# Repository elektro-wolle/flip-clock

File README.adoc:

= Copal Flip-Clock 

Antriebsrad (1 Umdrehung = 1 Stunde): ca. 82 Zähne  +
Stepper 12 Zähne  +
1 Minute = 6° * 82/11 = 41° Stepper 

Schritt-Schema: 3 Vollschritte zurück (Rutschkupplung nutzen) -> 1 Schritt vorwärts.

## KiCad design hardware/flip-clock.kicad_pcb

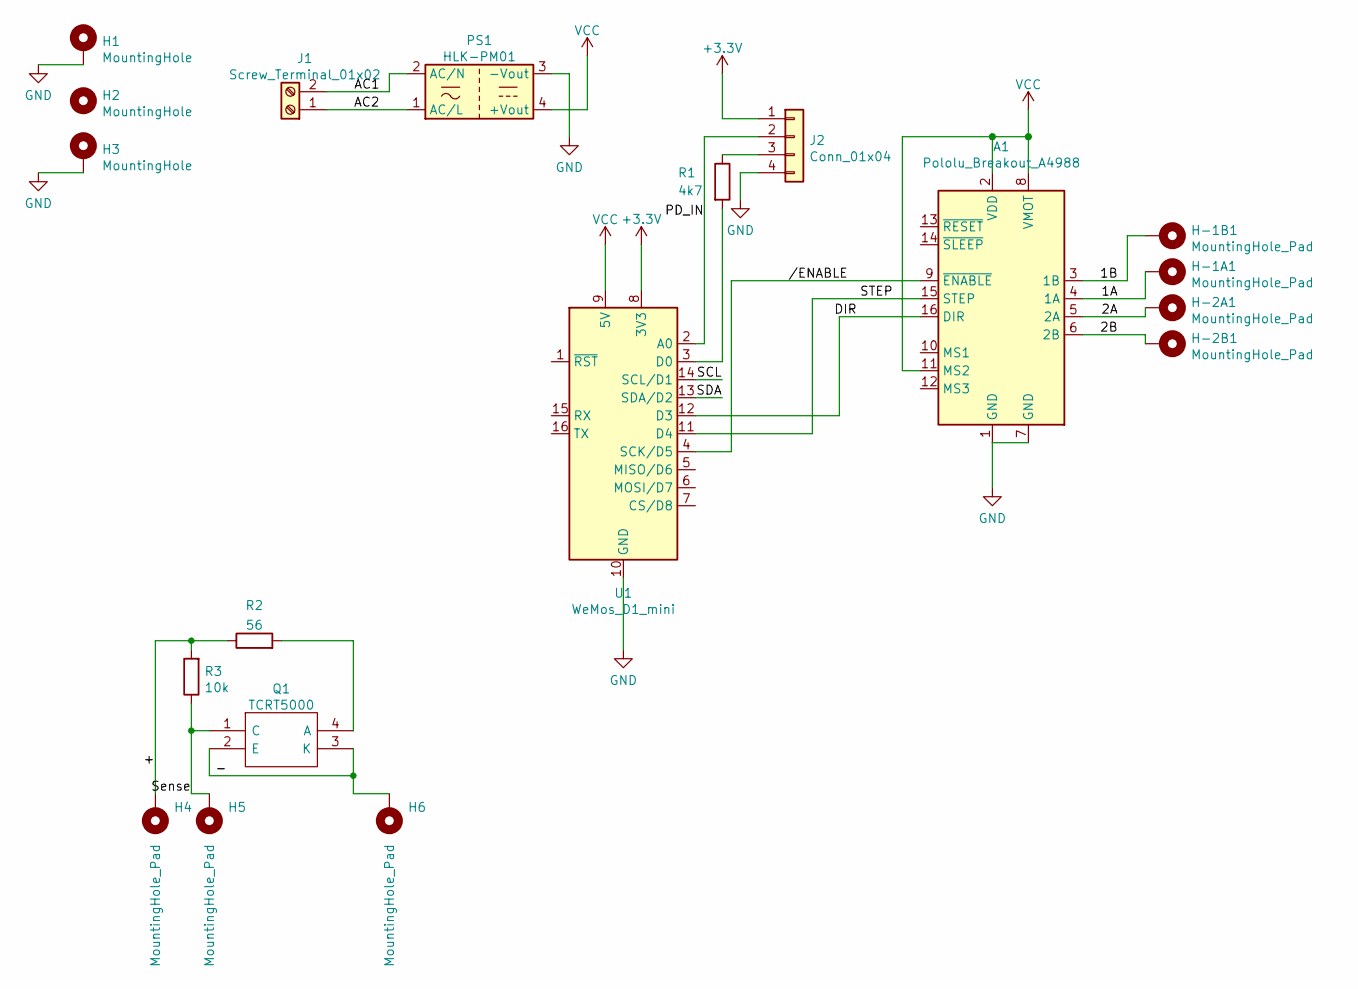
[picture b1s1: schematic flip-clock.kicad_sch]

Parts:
A1: Pololu_Breakout_A4988; Pololu_Breakout-16_15.2x20.3mm
H1, H3: MountingHole; MountingHole_3.2mm_M3_Pad
H2: MountingHole; MountingHole_5.3mm_M5
H4, H5, H6: MountingHole_Pad; SolderWirePad_1x01_SMD_1x2mm
H-1A1, H-1B1, H-2A1, H-2B1: MountingHole_Pad; SolderWire-0.1sqmm_1x01_D0.4mm_OD1mm
J1: Screw_Terminal_01x02; TerminalBlock_Phoenix_MKDS-1,5-2_1x02_P5.00mm_Horizontal
J2: Conn_01x04; JST_PH_B4B-PH-K_1x04_P2.00mm_Vertical
PS1: HLK-PM01; Converter_ACDC_HiLink_HLK-PMxx
Q1: TCRT5000; Manufacturer_Part_Number TCRT5000; Mouser Part Number 782-TCRT5000
R1: 4k7; R_0805_2012Metric
R2: 56; R_0805_2012Metric
R3: 10k; R_0805_2012Metric
U1: WeMos_D1_mini; WEMOS_D1_mini_light

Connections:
+3V3: J2.1, U1.8 (3V3)
/1A: A1.4 (1A), H-1A1.1
/1B: A1.3 (1B), H-1B1.1
/2A: A1.5 (2A), H-2A1.1
/2B: A1.6 (2B), H-2B1.1
/+: H4.1, R2.1, R3.2
/-: H6.1, Q1.2 (E), Q1.3 (K)
/AC1: J1.2, PS1.2 (AC/N)
/AC2: J1.1, PS1.1 (AC/L)
/DIR: A1.16 (DIR), U1.12 (D3)
/PD_IN: J2.2, U1.2 (A0)
/SCL: U1.14 (SCL/D1)
/SDA: U1.13 (SDA/D2)
/STEP: A1.15 (STEP), U1.11 (D4)
/Sense: H5.1, Q1.1 (C), R3.1
//ENABLE: A1.9 (~ENABLE), U1.4 (SCK/D5)
GND: A1.1 (GND), A1.7 (GND), H1.1, H3.1, J2.4, PS1.3 (-Vout), U1.10 (GND)
unnamed: J2.3, R1.1
unnamed: Q1.4 (A), R2.2
unnamed: R1.2, U1.3 (D0)
VCC: A1.2 (VDD), A1.8 (VMOT), A1.11 (MS2), PS1.4 (+Vout), U1.9 (5V)

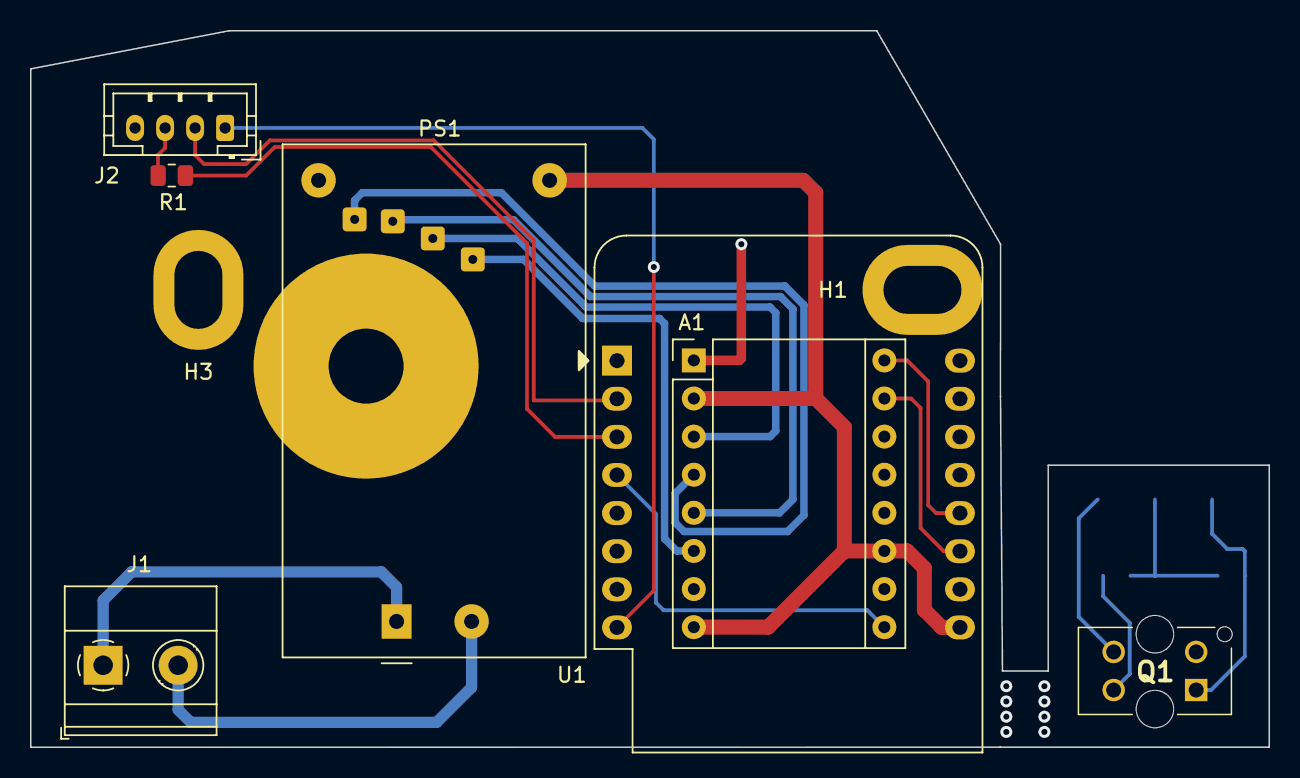
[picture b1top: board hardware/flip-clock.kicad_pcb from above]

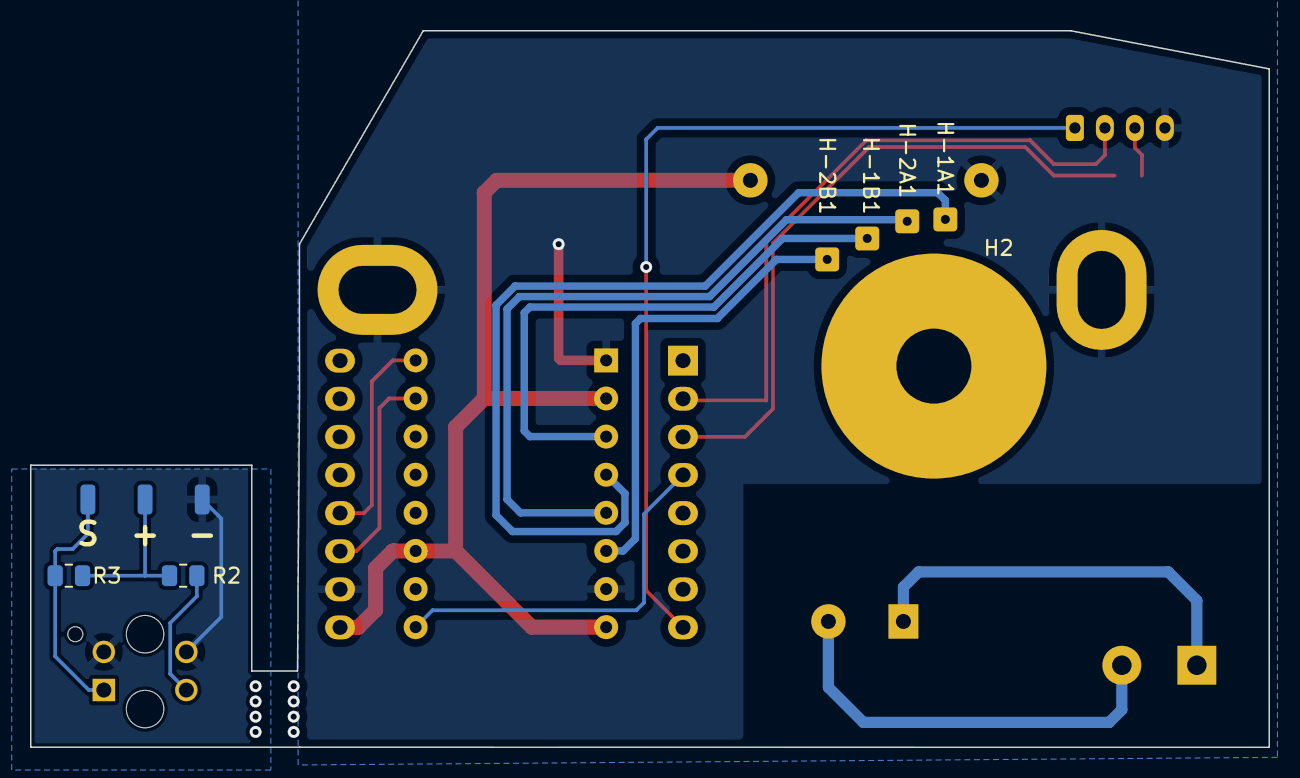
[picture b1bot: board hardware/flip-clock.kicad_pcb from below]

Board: 2 copper layers, 82.6 x 47.8 mm, 19 parts (6 on the bottom side), 19 nets.

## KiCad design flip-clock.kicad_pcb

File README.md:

Bei dieser schönen 60er-Jahre Uhr war der Synchronmotor defekt (lief nur
selten an, Versatz von 2h pro Tag). Ein Ersatz für diesen war nicht zu
finden, daher die High-Tech-Variante.

-   Synchronmotor durch Schrittmotor ersetzen

-   Zeit via NTP über einen ESP holen

-   Das Ganze so, dass es ein 1:1 Ersatz zu dem montierten Motor wird

# Herausforderungen

-   Einen Schrittmotor finden mit passendem Ritzel und passender Größe.

-   Der Schrittmotor mit passendem Ritzel ist für max. 5V ausgelegt, die
    üblichen StepSticks brauchen 8V.

-   Alles in das Gehäuse bekommen.

-   Erste Tests zeigten, dass für eine Minute eine unterschiedliche
    Anzahl an Schritten benötigt wird.

-   Keine Möglichkeit, das Umspringen der Minuten zu erkennen.

-   Spontane Abschaltungen bei Netzbetrieb.

# Lösungen

## Schrittmotor

AliExpress sei Dank: [Stepper-Motor mit 12 Zähnen und Modul
0,25](https://www.aliexpress.com/item/4001009328124.html).

## StepStick

Natürlich gibt es was von [Trinamic](https://www.trinamic.com) auf Basis
des [TMC2225
Datasheet](https://www.trinamic.com/fileadmin/assets/Products/ICs_Documents/TMC2225_Datasheet_Rev1.11.pdf).
Zum Beispiel [hier](https://www.amazon.de/dp/B08R3GFYTR).

## Platine produzieren

Millimetergenaues Ausmessen, KiCad, Aisler:

## Schritte zählen

Aufgrund des doch sehr beschränkten Platzes, blieb nur die Möglichkeit
übrig, die bestehende Glimmmlampe auszubauen und stattdessen eine kleine
Reflex-Lichtschranke (TCRT-5000) anzubringen. Diese löst recht
zuverlässig auf, wenn sich ein Blatt der Minuten-Anzeige im Fallen
befindet.

## Spontane Resets

Ein 100uF Kondensator auf der 5V Schiene wirkt Wunder:

## Fertiger Aufbau

## Zusammenbau

# Software

Kleines C++ Projekt mit platformio auf Basis der Bibliotheken:
[WiFiManager](https://github.com/tzapu/WiFiManager),
[AceTime](https://github.com/bxparks/AceTime),
[ESP_DoubleResetDetector](https://github.com/khoih-prog/ESP_DoubleResetDetector).

Lösung ist straight-forward: Intern wird die vermutlich angezeigte Zeit
(durch das Zählen via IR-Reflex-Lichtschranke) mit der via NTP
empfangenen Zeit verglichen und solange der Stepper-Motor aktiviert, bis
diese übereinstimmen.

Dabei eine Sonderbehandlung für kleine Abweichungen (bis 10 Minuten wird
einfach gewartet, bis die Zeit übereinstimmt) und in der Nacht (z.B. Bei
der Sommer-/Winterzeit-Umstellung müssten 23 Stunden nach vorne gestellt
werden).

Über eine minimale Web-Oberfläche kann bei Stromausfall oder ähnlichem
die tatsächlich angezeigte Uhrzeit angegeben werden. Code siehe
[Quellcode](sw/src/main.cpp).

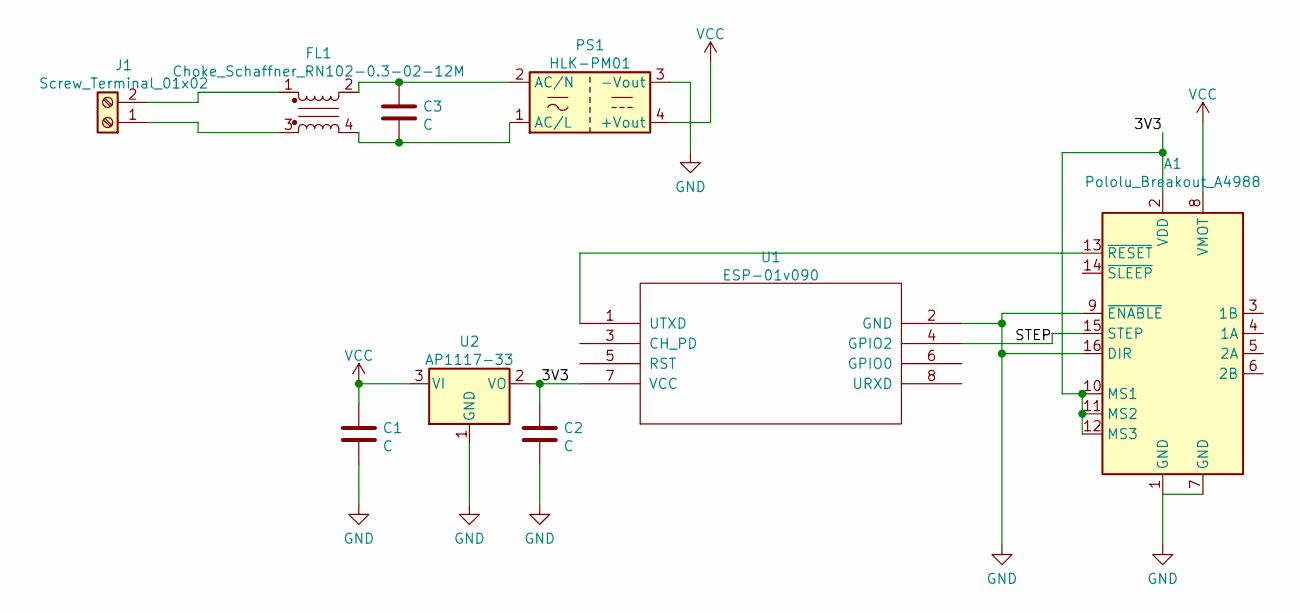
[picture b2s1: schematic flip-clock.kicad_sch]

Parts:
A1: Pololu_Breakout_A4988; Pololu_Breakout-16_15.2x20.3mm
C1, C2: C; C_0805_2012Metric
C3: C; C_Rect_L13.0mm_W6.0mm_P10.00mm_FKS3_FKP3_MKS4
FL1: Choke_Schaffner_RN102-0.3-02-12M; Choke_Schaffner_RN102-04-14.0x14.0mm
J1: Screw_Terminal_01x02; TerminalBlock_RND_205-00067_1x02_P7.50mm_Horizontal
PS1: HLK-PM01; Converter_ACDC_HiLink_HLK-2Mxx
U1: ESP-01v090; ESP-01
U2: AP1117-33; SOT-223-3_TabPin2

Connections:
/3V3: A1.2 (VDD), A1.10 (MS1), A1.11 (MS2), A1.12 (MS3), C2.1, U1.7 (VCC), U2.2 (VO)
/STEP: A1.15 (STEP), U1.4 (GPIO2)
GND: A1.1 (GND), A1.7 (GND), A1.9 (~ENABLE), A1.16 (DIR), C1.2, C2.2, PS1.3 (-Vout), U1.2 (GND), U2.1 (GND)
unnamed: A1.13 (~RESET), U1.1 (UTXD)
unnamed: FL1.1, J1.2
unnamed: FL1.3, J1.1
unnamed: C3.2, FL1.4, PS1.1 (AC/L)
unnamed: C3.1, FL1.2, PS1.2 (AC/N)
VCC: A1.8 (VMOT), C1.1, PS1.4 (+Vout), U2.3 (VI)

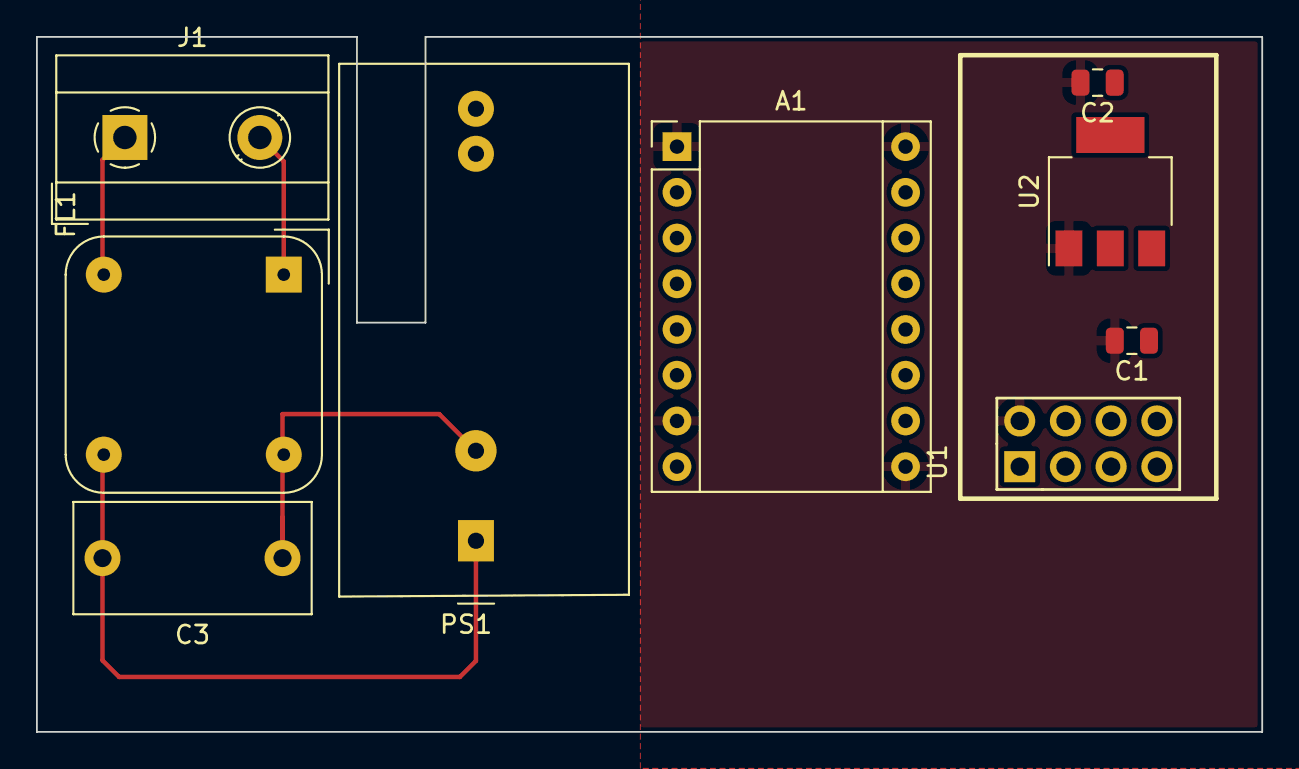
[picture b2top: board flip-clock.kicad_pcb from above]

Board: 2 copper layers, 68.1 x 38.6 mm, 9 parts (0 on the bottom side), 9 nets.

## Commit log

2021-04-09 initial
2021-04-09 Added 3D models
2021-04-19 Move kicad files to own directory
2021-05-09 Layout without choke
2021-05-11 Trapezoid Layout, Transformer in Front
2021-05-11 Wrong side populated
2021-05-11 Correct side
2021-05-12 Pre-Production
2021-05-13 Redesign after fitting probe
2021-05-14 Preview images
2021-05-15 JST Connector for IR and hour
2021-05-15 Lichtschranke hinzu
2021-05-15 second PCB-Part for IR
2021-06-03 Switched to TMC
2021-06-07 step until IR detects flip
2021-06-07 Missing net for flipped IR sensor
2022-01-24 Upgraded to kicad 6.0
2022-01-24 Adds correct handling of IR-Sensor and wifi
2022-01-24 New kicad version
2022-01-24 Adds double-reset and OTA
2022-01-25 Adds better delay-handling in loop()
2022-01-25 Adds missing MDNS update call
2022-01-25 Make serial output optional
2022-01-28 Use 3v3 as stable power supply for IR-Sensor
2022-01-28 Adds Logging for debugging random flips
2022-01-29 Adds Implementation for #1
2022-01-30 Allows TimeZone selection via web frontend
2022-01-30 Adds Blog-Post as README
2022-01-31 code-cleanup, better logging
2022-01-31 Better WebResponse Handling
2022-01-31 Optimization of flip-detection
2022-01-31 nicer html display
2022-02-02 More code-cleanup
2022-02-03 Adds graph of the last IR-Values
2022-02-03 Adds better assumption for detecting flipped minutes
2022-02-03 Makes trigger more sensitive
2022-02-05 Improves flip detection by measuring irValue/dt
2022-02-05 Assume, that missed triggers alreday flipped the minutes
2022-02-06 Adds detection of rising and falling edge
2022-02-07 Better small-rising edge detection
2022-02-10 Retry, if triggerCount too small
2022-02-12 Ensure small-up detection is only used, if there was no large falling edge
2023-03-26 remove obsolete file
